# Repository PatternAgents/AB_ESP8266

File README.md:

# AB_ESP8266
=============

**AB_ESP8266** is a Wi-Fi Interface that fits in a standard XBee socket. 

**Agent Bees** are standard XBEE socket implementations that implement
various reference and interface circuits compatible with the XBee ecosystem.
These reference designs can serve as starting templates for user designs.

**AB_ESP8266** includes an ESP8266-07 format Wi-Fi module,
and status LED's. 

---------------------------------------

For ESP8266 Documentation (esp. toolchain info) see [NurdSpace](https://nurdspace.nl/ESP8266)

[  
*AB_ESP8266*](https://github.com/patternagents/AB_ESP8266)

---------------------------------------

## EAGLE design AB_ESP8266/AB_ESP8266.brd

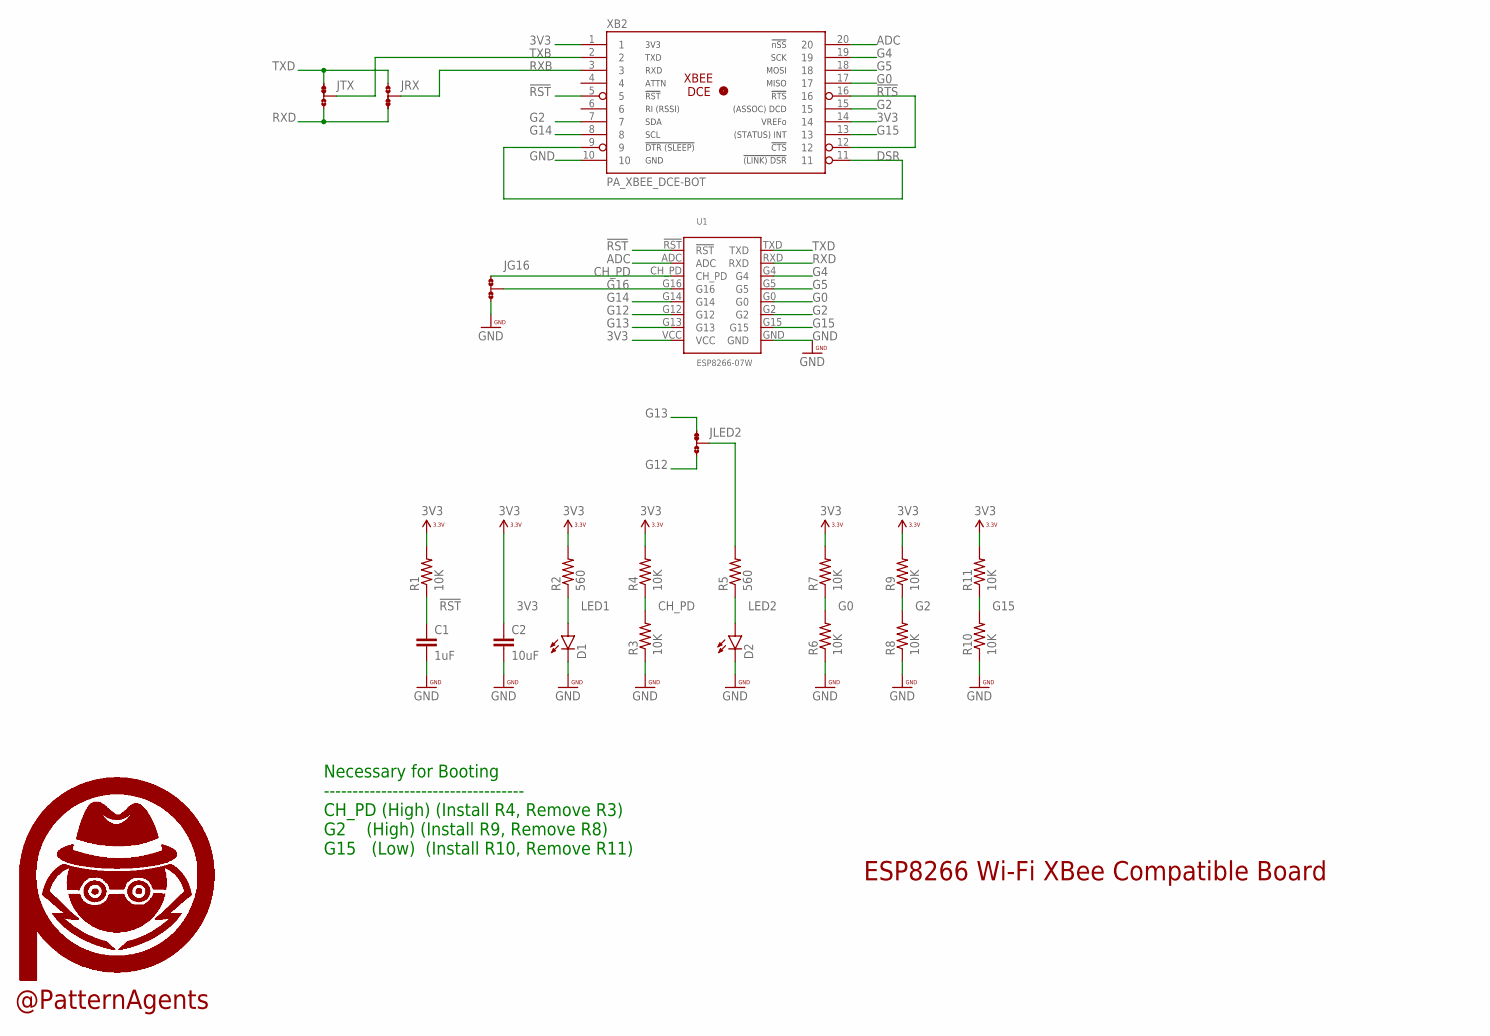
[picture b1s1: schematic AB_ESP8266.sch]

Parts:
C1: 1uF; 0603-CAP
C2: 10uF; 0603-CAP
D1, D2: LED0603; LED-0603
JG16: JMP-3-NO
JLED2: JMP-3-1_2
JRX: JMP-3-2_3
JTX: JMP-3-1_2
R1, R3, R4, R6, R7, R8, R9, R10, R11: 10K; 0603-RES
R2, R5: 560; 0603-RES
U1: ESP8266-07W
U$18, U$19: PA_LOGO_SYMSMALL; PA_LOGO_AGENT_SMALL_SYM
XB2: PA_XBEE_DCE-BOT; PA_XBEE_SMD_BOT

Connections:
3V3: C2.1, R1.2, R2.2, R4.2, R7.2, R9.2, R11.2, U1.VCC, XB2.1, XB2.14
!RST: C1.1, R1.1, U1.!RST, XB2.5
!RTS: XB2.12, XB2.16
ADC: U1.ADC, XB2.20
CH_PD: JG16.1, R3.2, R4.1, U1.CH_PD
DSR: XB2.9, XB2.11
G0: R6.2, R7.1, U1.G0, XB2.17
G2: R8.2, R9.1, U1.G2, XB2.7, XB2.15
G4: U1.G4, XB2.19
G5: U1.G5, XB2.18
G12: JLED2.3, U1.G12
G13: JLED2.1, U1.G13
G14: U1.G14, XB2.8
G15: R10.2, R11.1, U1.G15, XB2.13
G16: JG16.2, U1.G16
GND: C1.2, C2.2, D1.C, D2.C, JG16.3, R3.1, R6.1, R8.1, R10.1, U1.GND, XB2.10
JLED2: JLED2.2, R5.2
LED1: D1.A, R2.1
LED2: D2.A, R5.1
RXB: JRX.2, XB2.3
RXD: JRX.3, JTX.3, U1.RXD
TXB: JTX.2, XB2.2
TXD: JRX.1, JTX.1, U1.TXD

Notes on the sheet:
Necessary for Booting ----------------------------------- CH_PD (High) (Install R4, Remove R3) G2 (High) (Install R9, Remove R8) G15 (Low) (Install R10, Remove R11)
ESP8266 Wi-Fi XBee Compatible Board
@PatternAgents

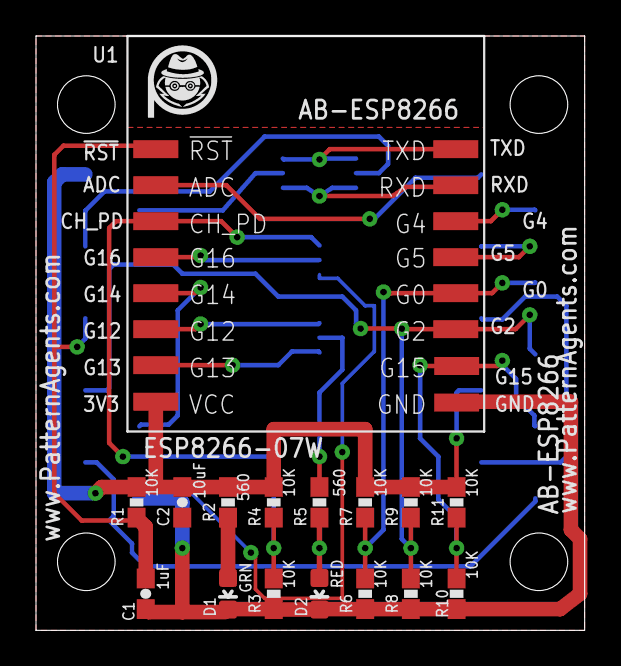
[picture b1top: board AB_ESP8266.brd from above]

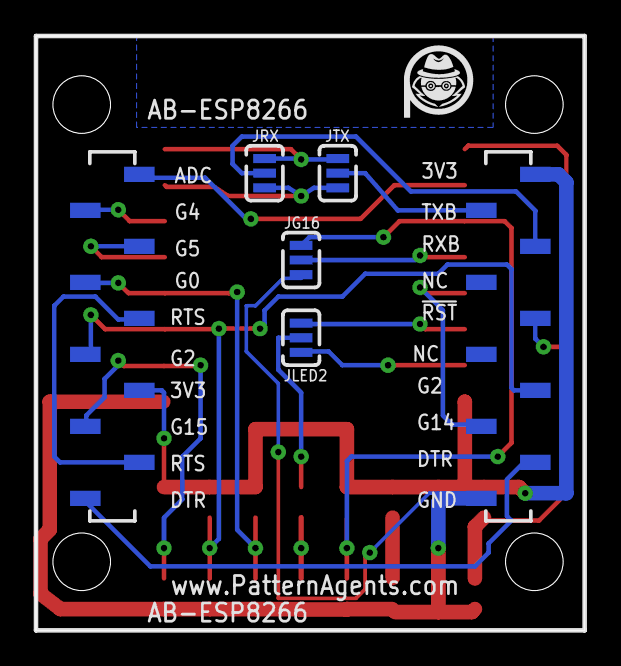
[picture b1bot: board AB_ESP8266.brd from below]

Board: 2 copper layers, 30.5 x 33.0 mm, 23 parts (5 on the bottom side), 23 nets.

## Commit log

2015-06-20 initial version

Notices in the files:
parts and their libraries:
PatternAgents-Interface: License : http://creativecommons.org/licenses/by-sa/4.0
(Creative Commons 4.0)
SparkFun-LED: Licensing: Creative Commons ShareAlike 4.0 International - https://creativecommons.org/licenses/by-sa/4.0
